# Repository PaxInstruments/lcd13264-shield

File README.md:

# Pax Instruments
# LCD12364-shield

[Pax Instruments Template Module](<link to store page>)

## Overview
The Pax Instruments LCD12364-shield is an Arduino shield for the Pax Instruments LCD23164 graphic LCD. You can [purchase this item in our store](http://paxinstruments.com/products/sku1003/).

## Repository Contents
- __Datasheets__ - Datasheets for relevant components and parts
- __Electronics__ - All PCB and schematic design files
- __Enclosure__ - Enclosure 3D design files
- __Firmware__ - Firmware, libraries, and examples
- __Production__ - Manufacturing resources
- __Resources__ - Other resources

## Product Versions

## License Information
```
Place the license statement here
```

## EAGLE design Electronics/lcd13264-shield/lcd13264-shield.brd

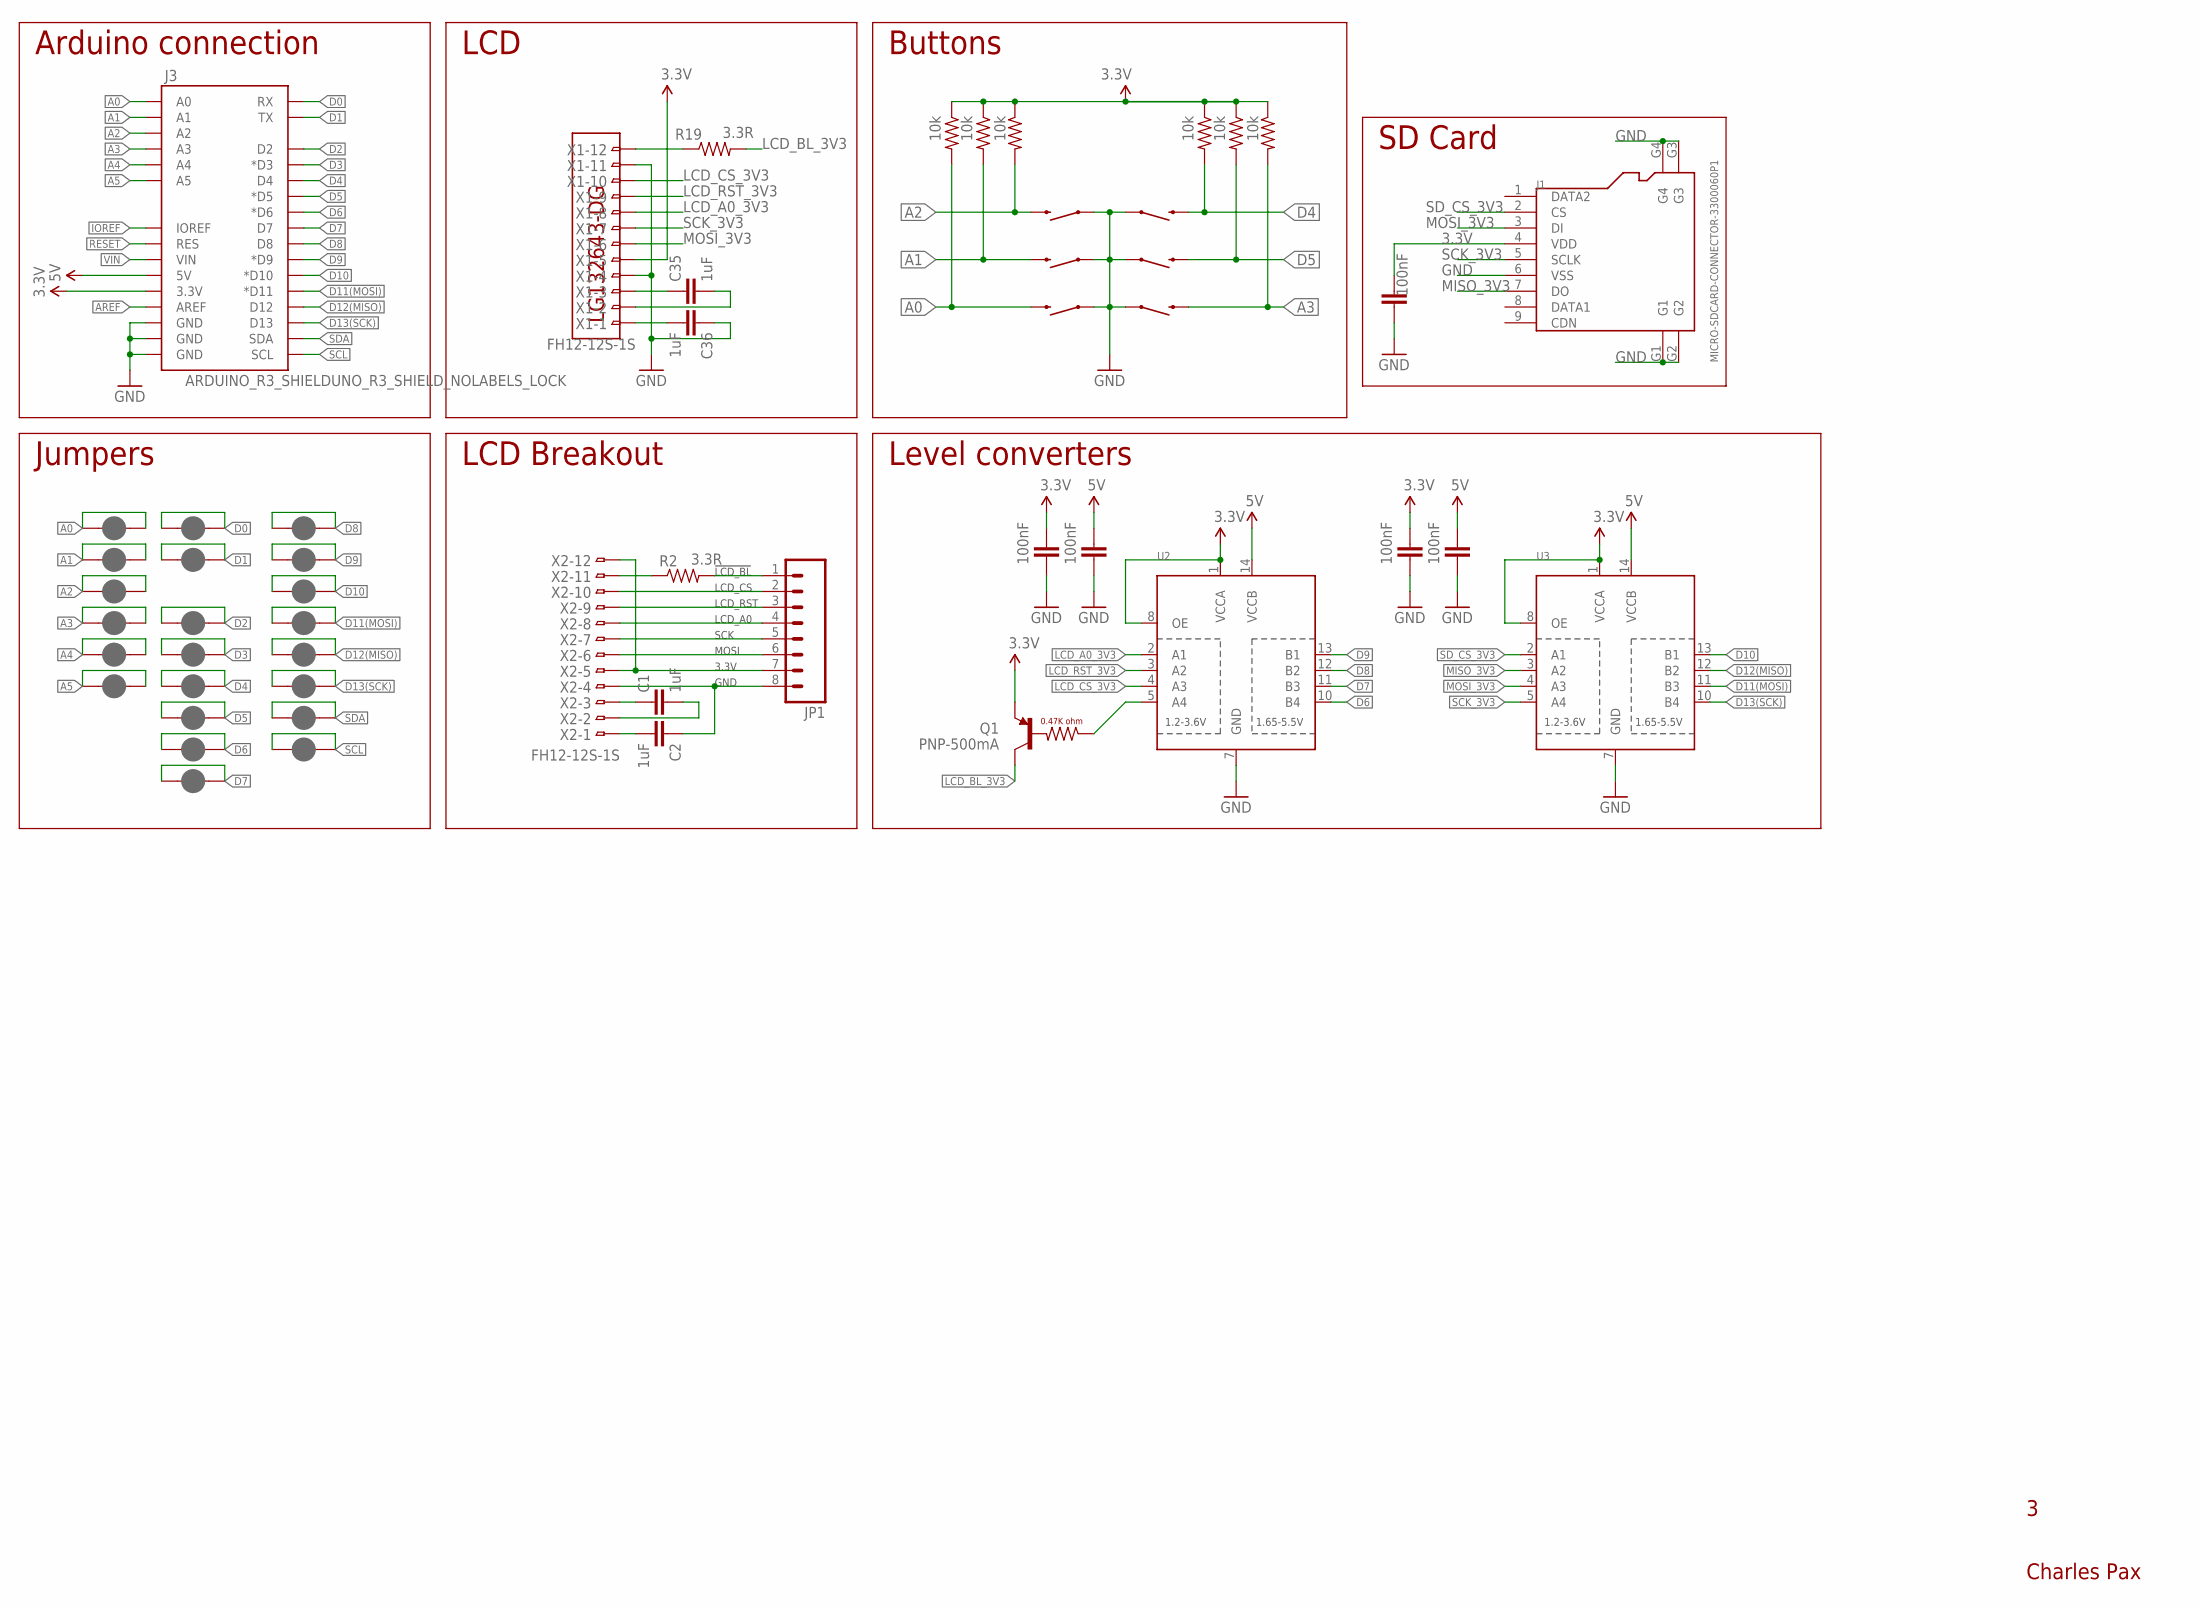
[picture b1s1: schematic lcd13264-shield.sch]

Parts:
C1, C2, C35, C36: 1uF; SPARKFUN-CAPACITORS_0603-CAP; MPN LMK107B7105KA-T
C3, C4, C5, C6, C21: 100nF; SPARKFUN-CAPACITORS_0603-CAP; MPN CL10B104KO8NNNC
J1: MICRO-SDCARD-CONNECTOR-3300060P1; 9P-SMD-W-RING
J3: ARDUINO_R3_SHIELDUNO_R3_SHIELD_NOLABELS_LOCK; UNO_R3_SHIELD_NOLABELS_LOCK
JP1: M08; 1X08_ROUND
Q1: PNP-500mA; SOT23-3; MPN DDTB142TC
R1, R8, R11, R12, R15, R16: 10k; SPARKFUN-RESISTORS_0603-RES; MPN RC1608J103CS
R2, R19: 3.3R; SPARKFUN-RESISTORS_0603-RES
S1, S2, S3, S4, S5, S6: SWITCH-MOMENTARY-2SMD; TACTILE_SWITCH_SMD
SJ1, SJ2, SJ3, SJ4, SJ5, SJ6, SJ7, SJ8, SJ9, SJ10, SJ11, SJ12, SJ13, SJ14, SJ19, SJ20, SJ21, SJ22, SJ23, SJ24, SJ25, SJ26: JUMPER-PAD-2-NC_BY_PASTE; PAD-JUMPER-2-NC_BY_PASTE_YES_SILK
U2, U3: TXB0104PWRSOIC14; SO14; MPN TXB0104DR
U$5: LG132643-DG; MPN LG132643-DW
X1, X2: FH12-12S-1S; FH12-12S-1SH

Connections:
3.3V: C3.2, C5.2, C21.2, J1.4 (VDD), J3.3.3V, Q1.2 (E), R1.1, R8.1, R11.1, R12.1, R15.1, R16.1, U2.1 (VCCA), U2.8 (OE), U3.1 (VCCA), U3.8 (OE), X1.5
5V: C4.2, C6.2, J3.5V, U2.14 (VCCB), U3.14 (VCCB)
A0: J3.A0, R1.2, S6.3 (2), SJ10.1, SJ10.2
A1: J3.A1, R16.2, S5.3 (2), SJ7.1, SJ7.2
A2: J3.A2, R15.2, S4.3 (2), SJ11.1, SJ11.2
A3: J3.A3, R12.2, S1.3 (2), SJ12.1, SJ12.2
A4: J3.A4, SJ13.1, SJ13.2
A5: J3.A5, SJ14.1, SJ14.2
AREF: J3.AREF
D0: J3.RX, SJ8.1, SJ8.2
D1: J3.TX, SJ9.1, SJ9.2
D2: J3.D2, SJ3.1, SJ3.2
D3: J3.D3 (*D3), SJ4.1, SJ4.2
D4: J3.D4, R8.2, S3.3 (2), SJ5.1, SJ5.2
D5: J3.D5 (*D5), R11.2, S2.3 (2), SJ6.1, SJ6.2
D6: J3.D6 (*D6), SJ19.1, SJ19.2, U2.10 (B4)
D7: J3.D7, SJ20.1, SJ20.2, U2.11 (B3)
D8: J3.D8, SJ21.1, SJ21.2, U2.12 (B2)
D9: J3.D9 (*D9), SJ22.1, SJ22.2, U2.13 (B1)
D10: J3.D10 (*D10), SJ23.1, SJ23.2, U3.13 (B1)
D11(MOSI): J3.D11 (*D11), SJ24.1, SJ24.2, U3.11 (B3)
D12(MISO): J3.D12, SJ25.1, SJ25.2, U3.12 (B2)
D13(SCK): J3.D13, SJ26.1, SJ26.2, U3.10 (B4)
GND: C2.1, C3.1, C4.1, C5.1, C6.1, C21.1, C36.1, J1.6 (VSS), J1.G1, J1.G2, J1.G3, J1.G4, J3.GND@0 (GND), J3.GND@1 (GND), J3.GND@2 (GND), JP1.8, S1.1, S2.1, S3.1, S4.1, S5.1, S6.1, U2.7 (GND), U3.7 (GND), X1.4, X1.11, X2.4
IOREF: J3.IOREF
LCD_A0_3V3: U2.2 (A1), X1.8
LCD_BL_3V3: Q1.3 (C), R19.2
LCD_CS_3V3: U2.4 (A3), X1.10
LCD_RST_3V3: U2.3 (A2), X1.9
MISO_3V3: J1.7 (DO), U3.3 (A2)
MOSI_3V3: J1.3 (DI), U3.4 (A3), X1.6
unnamed: R19.1, X1.12
unnamed: C35.1, X1.3
unnamed: C35.2, X1.2
unnamed: C36.2, X1.1
unnamed: C1.1, X2.3
unnamed: C1.2, X2.2
unnamed: C2.2, X2.1
unnamed: R2.1, X2.11
unnamed: JP1.7, X2.5, X2.12
unnamed: JP1.1, R2.2
unnamed: JP1.2, X2.10
unnamed: JP1.3, X2.9
unnamed: JP1.4, X2.8
unnamed: JP1.5, X2.7
unnamed: JP1.6, X2.6
unnamed: Q1.1 (B), U2.5 (A4)
RESET: J3.RES
SCK_3V3: J1.5 (SCLK), U3.5 (A4), X1.7
SCL: J3.SCL, SJ2.1, SJ2.2
SDA: J3.SDA, SJ1.1, SJ1.2
SD_CS_3V3: J1.2 (CS), U3.2 (A1)
VIN: J3.VIN

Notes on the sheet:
LCD
Buttons
Charles Pax
SD Card
Arduino connection
LCD Breakout
GND
3.3V
MOSI
SCK
LCD_A0
LCD_RST
LCD_CS
!LCD_BL
Level converters
Jumpers

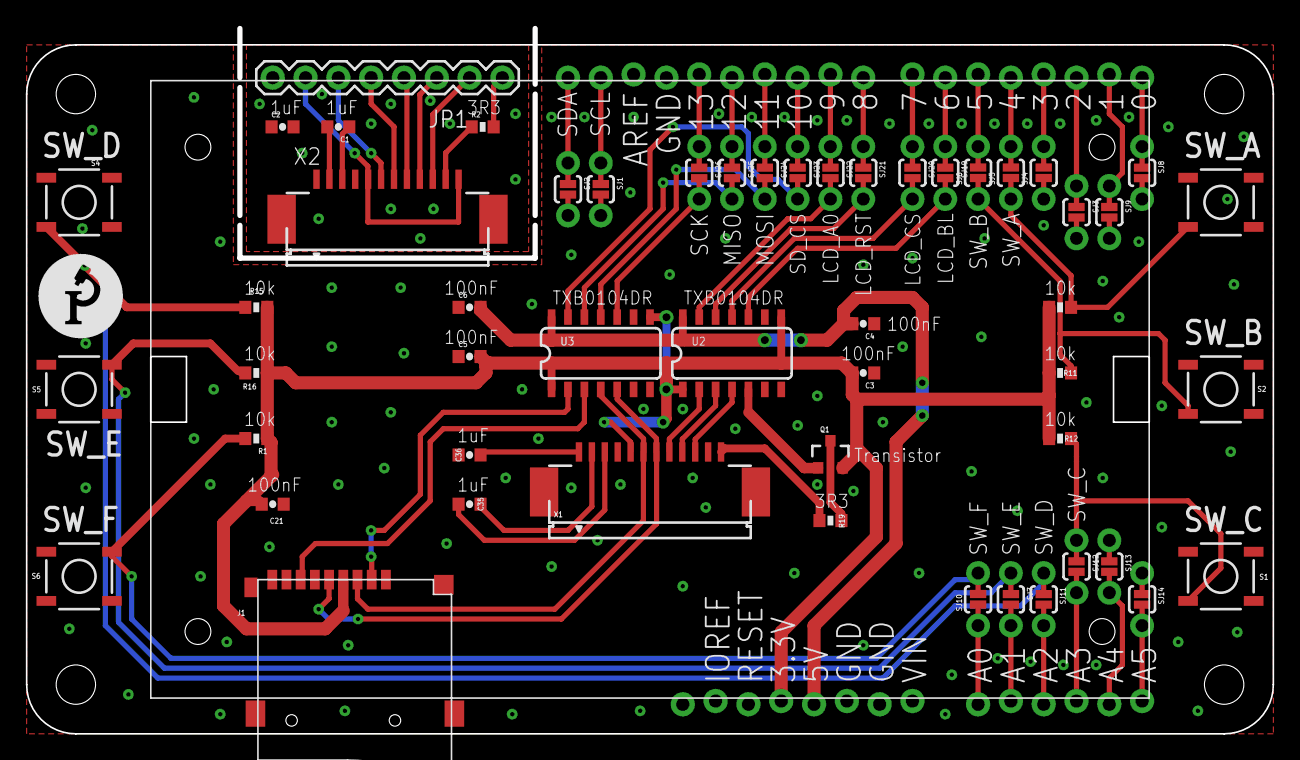
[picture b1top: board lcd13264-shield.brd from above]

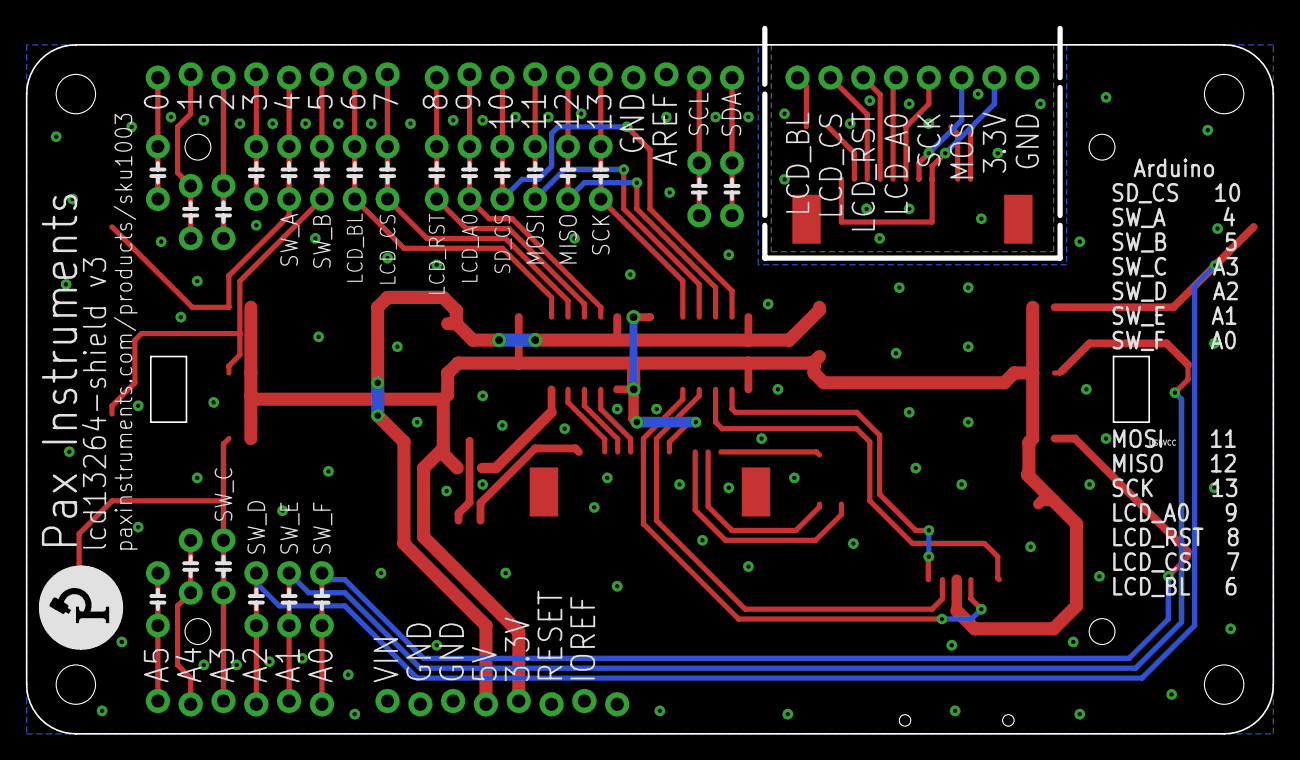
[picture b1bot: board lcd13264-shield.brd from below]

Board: 2 copper layers, 96.5 x 54.6 mm, 56 parts (2 on the bottom side), 49 nets.

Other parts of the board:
U$1, U$6: PAXINSTRUMENT_LOGO

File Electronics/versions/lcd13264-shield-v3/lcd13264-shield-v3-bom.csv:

"Qty";"Value";"Device";"Package";"Parts";"Description";"MPN";"OC_DIGIKEY";"PROD_ID";"VALUE";
"1";"";"M08";"1X08_ROUND";"JP1";"Header 8";"";"";"";"";
"2";"";"TXB0104PWRSOIC14";"SO14";"U2, U3";"4-Bit Bi-Directional Level Shifter";"";"";"IC-11329";"";
"5";"100nF";"SPARKFUN-CAPACITORS_CAP0603-CAP";"SPARKFUN-CAPACITORS_0603-CAP";"C3, C4, C5, C6, C21";"Capacitor";"CL10B104KO8NNNC";"1276-1005-2-ND";"";"";
"6";"10k";"SPARKFUN-RESISTORS_RESISTOR0603-RES";"SPARKFUN-RESISTORS_0603-RES";"R1, R8, R11, R12, R15, R16";"Resistor";"RC1608J103CS";"1276-5086-2-ND";"";"";
"4";"1uF";"SPARKFUN-CAPACITORS_CAP0603-CAP";"SPARKFUN-CAPACITORS_0603-CAP";"C1, C2, C35, C36";"Capacitor";"LMK107B7105KA-T";"587-1242-2-ND";"";"";
"2";"3.3R";"SPARKFUN-RESISTORS_RESISTOR0603-RES";"SPARKFUN-RESISTORS_0603-RES";"R2, R19";"Resistor";"";"";"";"";
"1";"ARDUINO_R3_SHIELDUNO_R3_SHIELD_NOLABELS_LOCK";"ARDUINO_R3_SHIELDUNO_R3_SHIELD_NOLABELS_LOCK";"UNO_R3_SHIELD_NOLABELS_LOCK";"J3";"Shield form compatible with the Arduino Uno R3.";"";"";"";"";
"2";"FH12-12S-1S";"FH12-12S-1S";"FH12-12S-1SH";"X1, X2";"";"";"";"";"";
"22";"JUMPER-PAD-2-NC_BY_PASTE";"JUMPER-PAD-2-NC_BY_PASTE";"PAD-JUMPER-2-NC_BY_PASTE_YES_SILK";"SJ1, SJ2, SJ3, SJ4, SJ5, SJ6, SJ7, SJ8, SJ9, SJ10, SJ11, SJ12, SJ13, SJ14, SJ19, SJ20, SJ21, SJ22, SJ23, SJ24, SJ25, SJ26";"";"";"";"";"";
"1";"LG132643-DG";"LG132643-DG";"LG132643-DG";"U$5";"";"LG132643-DW";"";"";"";
"1";"MICRO-SDCARD-CONNECTOR-3300060P1";"MICRO-SDCARD-CONNECTOR-3300060P1";"9P-SMD-W-RING";"J1";"Micro SD Card";"";"";"";"";
"1";"PNP-500mA";"TRANSISTOR-PNP-DDTB142TC";"SOT23-3";"Q1";"PNP transistor with base resistor.";"";"";"TRANS-11479";"PNP-500mA";
"6";"SWITCH-MOMENTARY-2SMD";"SWITCH-MOMENTARY-2SMD";"TACTILE_SWITCH_SMD";"S1, S2, S3, S4, S5, S6";"Various NO switches- pushbuttons, reed, etc";"";"";"";"";

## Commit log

2015-04-16 Initial commit.
2015-04-16 Routed baord. Need to put on finishing touches.
2015-04-16 Revied and modified PCB for ordering. Initiated a v1 version. Added CAM file.
2015-04-18 Updated the LCD connector.
2015-04-20 Added component tags to PCB (more needed). Added firmware.
2015-04-20 Firmware tests each button, prints to LCD, and fades the backlight.
2015-04-20 SD test works. Hold down C and D.
2015-04-20 Added bypass caps to level shifter. This closes #1.
2015-04-22 Aupdated shield. Not sure what.
2015-04-26 Close to done. Need to review.
2015-04-26 This version is done. CAM next...
2015-04-26 Added v2 gerber files.
2015-04-29 SW_D now more responsive.
2015-05-02 Changed all passives to 0805 and updated traces. Passes DRC.
2015-05-02 Decreased breakout board snap size.
2015-05-02 Reorganized the versions gerbers.
2015-05-02 Renamed some files.
2015-05-02 Closed all the silkscreen issues.
2015-05-02 Added pin function labels to top and bottom. Verified silkscreen.
2015-05-02 Added version 3 gerbers.
2015-05-03 Added MPN for LCD_BL PNP transistor.
2015-05-03 Updated the example firmware. LCD on by default. Fading is smoother.
2015-05-05 Corrected the transistor value. We are using a transistor with built-in base resistor.
2015-05-05 Added active low notation to LCD_BL.
2015-05-09 Added psrt numbers.
2016-04-30 Unknown changes.

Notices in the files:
parts and their libraries:
SparkFun-Electromechanical: Licensing: CC v3.0 Share-Alike You are welcome to use this library for commercial purposes.
SparkFun-Boards: Licensing: Creative Commons ShareAlike 4.0 International - https://creativecommons.org/licenses/by-sa/4.0
